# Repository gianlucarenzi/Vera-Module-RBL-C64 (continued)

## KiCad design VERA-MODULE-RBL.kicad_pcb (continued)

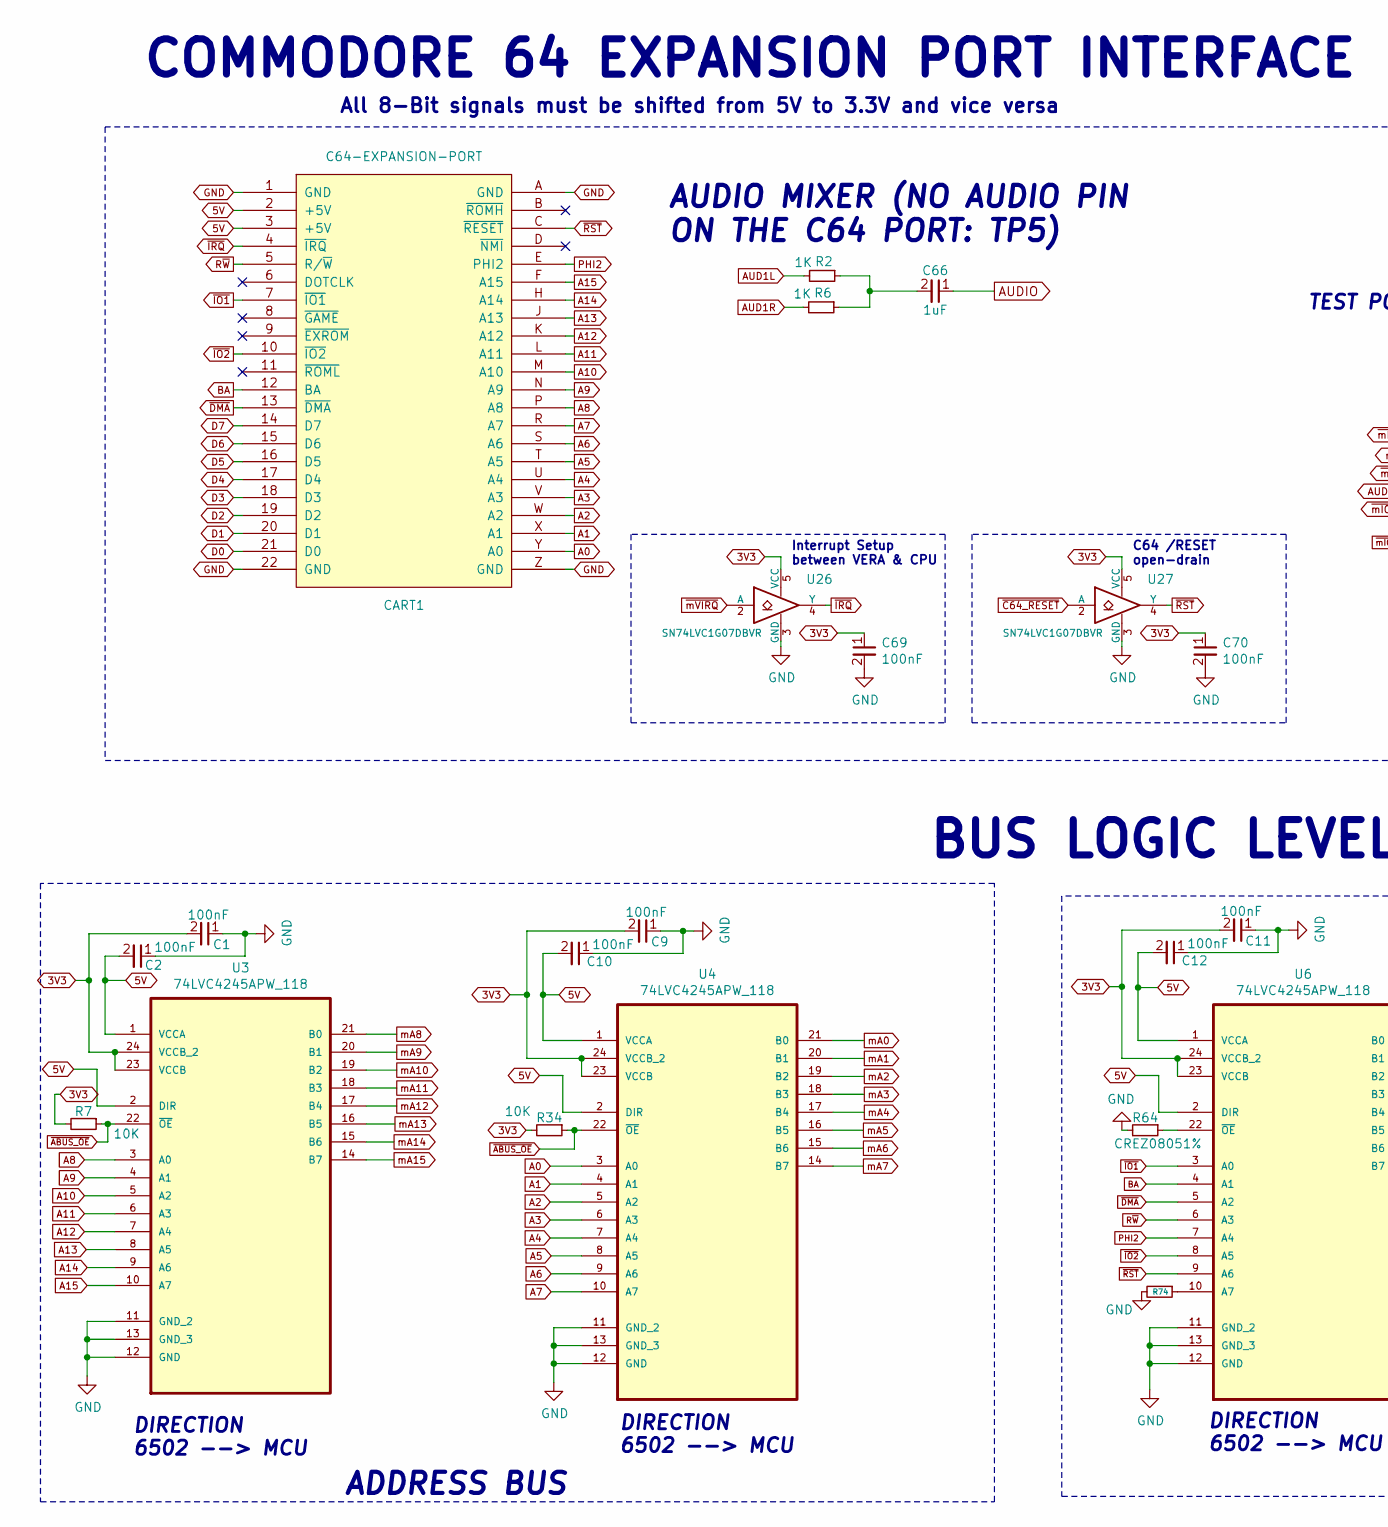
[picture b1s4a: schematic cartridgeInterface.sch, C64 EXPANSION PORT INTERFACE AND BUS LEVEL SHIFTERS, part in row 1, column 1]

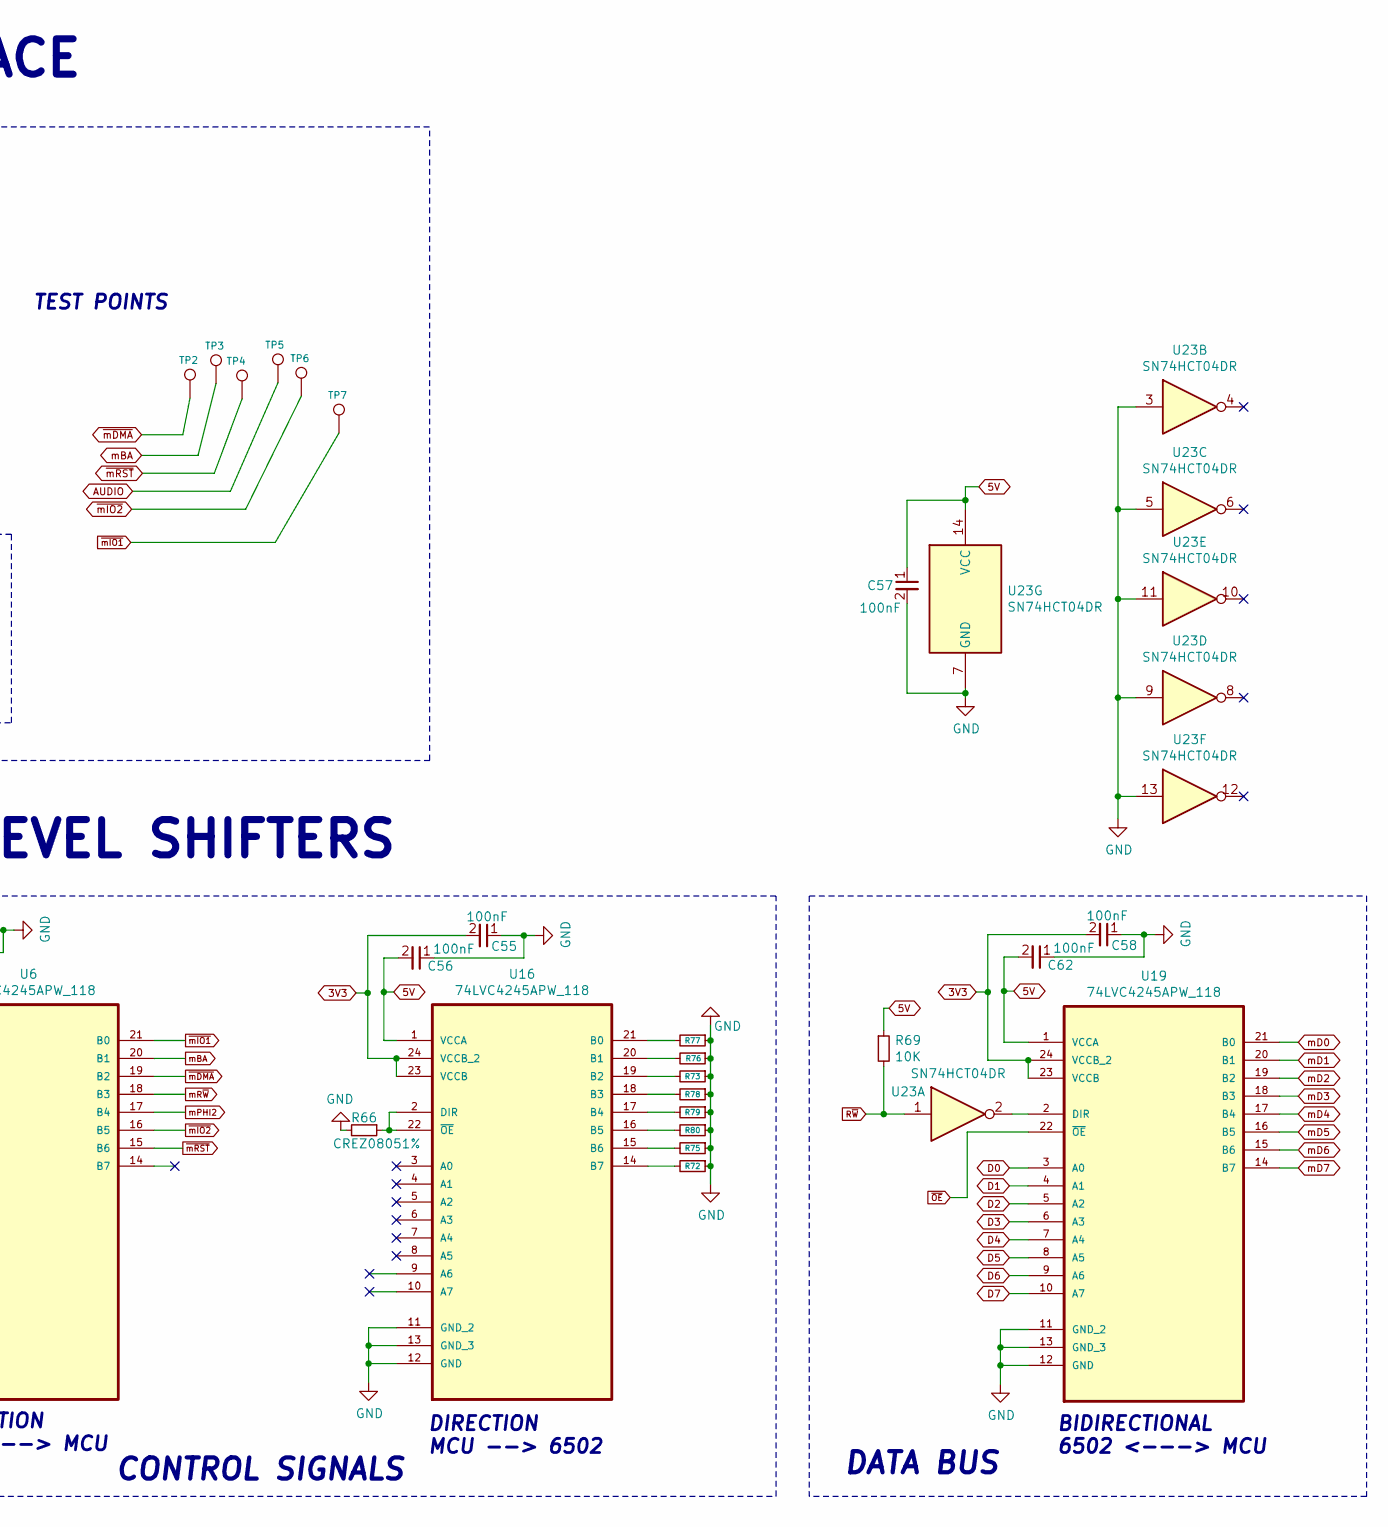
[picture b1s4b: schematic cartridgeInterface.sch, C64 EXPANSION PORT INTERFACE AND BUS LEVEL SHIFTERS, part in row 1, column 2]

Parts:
C1, C2, C9, C10, C11, C12, C55, C56, C57, C58, C62, C69, C70: 100nF; C_0805_2012Metric_Pad1.18x1.45mm_HandSolder; LCSC C840116
C66: 1uF; C_0805_2012Metric_Pad1.18x1.45mm_HandSolder; LCSC C2798196
CART1: C64-EXPANSION-PORT; C64-EXPANSION-CARTRIDGE
R2, R6: 1K; R_0805_2012Metric_Pad1.20x1.40mm_HandSolder; LCSC C17513
R7, R34, R69: 10K; R_0805_2012Metric_Pad1.20x1.40mm_HandSolder; LCSC C84376
R64, R66, R72, R73, R74, R75, R76, R77, R78, R79, R80: CREZ08051%; R_0805_2012Metric_Pad1.20x1.40mm_HandSolder; LCSC C328378
TP2, TP3, TP4, TP5, TP6, TP7: TestPoint; TestPoint_Pad_D2.0mm
U3, U4, U6, U16, U19: 74LVC4245APW_118; IC_74LVC4245_SOP65P640X110-24N; LCSC C6091
U23: SN74HCT04DR; SOIC-14_3.9x8.7mm_P1.27mm; LCSC C6766
U26, U27: SN74LVC1G07DBVR; SOT-23-5; LCSC C7829

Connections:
3V3: C1.2, C9.2, C11.2, C55.2, C58.2, C69.1, C70.1, R7.2, R34.2, U3.23 (VCCB), U3.24 (VCCB_2), U4.23 (VCCB), U4.24 (VCCB_2), U6.23 (VCCB), U6.24 (VCCB_2), U16.23 (VCCB), U16.24 (VCCB_2), U19.23 (VCCB), U19.24 (VCCB_2), U26.5 (VCC), U27.5 (VCC); also elsewhere on the board
5V: C2.2, C10.2, C12.2, C56.2, C57.1, C62.2, CART1.2 (+5V), CART1.3 (+5V), R69.1, U3.1 (VCCA), U3.2 (DIR), U4.1 (VCCA), U4.2 (DIR), U6.1 (VCCA), U6.2 (DIR), U16.1 (VCCA), U19.1 (VCCA), U23.14 (VCC); also elsewhere on the board
A0: CART1.Y (A0), U4.3 (A0)
A1: CART1.X (A1), U4.4 (A1)
A2: CART1.W (A2), U4.5 (A2)
A3: CART1.V (A3), U4.6 (A3)
A4: CART1.U (A4), U4.7 (A4)
A5: CART1.T (A5), U4.8 (A5)
A6: CART1.S (A6), U4.9 (A6)
A7: CART1.R (A7), U4.10 (A7)
A8: CART1.P (A8), U3.3 (A0)
A9: CART1.N (A9), U3.4 (A1)
A10: CART1.M (A10), U3.5 (A2)
A11: CART1.L (A11), U3.6 (A3)
A12: CART1.K (A12), U3.7 (A4)
A13: CART1.J (A13), U3.8 (A5)
A14: CART1.H (A14), U3.9 (A6)
A15: CART1.F (A15), U3.10 (A7)
AUD1L: R2.2; also elsewhere on the board
AUD1R: R6.2; also elsewhere on the board
AUDIO: C66.1, TP5.1
BA: CART1.12 (BA), U6.4 (A1)
D0: CART1.21 (D0), U19.3 (A0)
D1: CART1.20 (D1), U19.4 (A1)
D2: CART1.19 (D2), U19.5 (A2)
D3: CART1.18 (D3), U19.6 (A3)
D4: CART1.17 (D4), U19.7 (A4)
D5: CART1.16 (D5), U19.8 (A5)
D6: CART1.15 (D6), U19.9 (A6)
D7: CART1.14 (D7), U19.10 (A7)
GND: C1.1, C2.1, C9.1, C10.1, C11.1, C12.1, C55.1, C56.1, C57.2, C58.1, C62.1, C69.2, C70.2, CART1.1 (GND), CART1.22 (GND), CART1.A (GND), CART1.Z (GND), R64.2, R66.2, R72.1, R73.1, R74.2, R75.1, R76.1, R77.1, R78.1, R79.1, R80.1, U3.11 (GND_2), U3.12 (GND), U3.13 (GND_3), U4.11 (GND_2), U4.12 (GND), U4.13 (GND_3), U6.11 (GND_2), U6.12 (GND), U6.13 (GND_3), U16.11 (GND_2), U16.12 (GND), U16.13 (GND_3), U19.11 (GND_2), U19.12 (GND), U19.13 (GND_3), U23.3, U23.5, U23.7 (GND), U23.9, U23.11, U23.13, U26.3 (GND), U27.3 (GND); also elsewhere on the board
unnamed: C66.2, R2.1, R6.1
unnamed: R64.1, U6.22 (~OE)
unnamed: R66.1, U16.2 (DIR), U16.22 (~OE)
unnamed: R72.2, U16.14 (B7)
unnamed: R73.2, U16.19 (B2)
unnamed: R74.1, U6.10 (A7)
unnamed: R75.2, U16.15 (B6)
unnamed: R76.2, U16.20 (B1)
unnamed: R77.2, U16.21 (B0)
unnamed: R78.2, U16.18 (B3)
unnamed: R79.2, U16.17 (B4)
unnamed: R80.2, U16.16 (B5)
unnamed: U19.2 (DIR), U23.2
PHI2: CART1.E (PHI2), U6.7 (A4)
R~W: CART1.5 (R/~W), R69.2, U6.6 (A3), U23.1
mA0: U4.21 (B0); also elsewhere on the board
mA1: U4.20 (B1); also elsewhere on the board
mA2: U4.19 (B2); also elsewhere on the board
mA3: U4.18 (B3); also elsewhere on the board
mA4: U4.17 (B4); also elsewhere on the board
mA5: U4.16 (B5); also elsewhere on the board
mA6: U4.15 (B6); also elsewhere on the board
mA7: U4.14 (B7); also elsewhere on the board
mA8: U3.21 (B0); also elsewhere on the board
mA9: U3.20 (B1); also elsewhere on the board
mA10: U3.19 (B2); also elsewhere on the board
mA11: U3.18 (B3); also elsewhere on the board
mA12: U3.17 (B4); also elsewhere on the board
mA13: U3.16 (B5); also elsewhere on the board
mA14: U3.15 (B6); also elsewhere on the board
mA15: U3.14 (B7); also elsewhere on the board
mBA: TP3.1, U6.20 (B1)
mD0: U19.21 (B0); also elsewhere on the board
mD1: U19.20 (B1); also elsewhere on the board
mD2: U19.19 (B2); also elsewhere on the board
mD3: U19.18 (B3); also elsewhere on the board
mD4: U19.17 (B4); also elsewhere on the board
mD5: U19.16 (B5); also elsewhere on the board
mD6: U19.15 (B6); also elsewhere on the board
mD7: U19.14 (B7); also elsewhere on the board
mPHI2: U6.17 (B4); also elsewhere on the board
mR~W: U6.18 (B3); also elsewhere on the board
~ABUS_OE: R7.1, R34.1, U3.22 (~OE), U4.22 (~OE); also elsewhere on the board
~C64_RESET: U27.2 (A); also elsewhere on the board
~DMA: CART1.13 (~DMA), U6.5 (A2)
~IO1: CART1.7 (~IO1), U6.3 (A0)
~IO2: CART1.10 (~IO2), U6.8 (A5)
~IRQ: CART1.4 (~IRQ), U26.4 (Y)
~OE: U19.22 (~OE); also elsewhere on the board
~RST: CART1.C (~RESET), U6.9 (A6), U27.4 (Y)
~mDMA: TP2.1, U6.19 (B2)
~mIO1: TP7.1, U6.21 (B0); also elsewhere on the board
~mIO2: TP6.1, U6.16 (B5); also elsewhere on the board
~mRST: TP4.1, U6.15 (B6)
~mVIRQ: U26.2 (A); also elsewhere on the board

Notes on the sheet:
COMMODORE 64 EXPANSION PORT INTERFACE
All 8-Bit signals must be shifted from 5V to 3.3V and vice versa
TEST POINTS
BUS LOGIC LEVEL SHIFTERS
DIRECTION 6502 --> MCU
DIRECTION MCU --> 6502
BIDIRECTIONAL 6502 <---> MCU
CONTROL SIGNALS
ADDRESS BUS
DATA BUS
Interrupt Setup between VERA & CPU
C64 /RESET open-drain
AUDIO MIXER (NO AUDIO PIN ON THE C64 PORT: TP5)

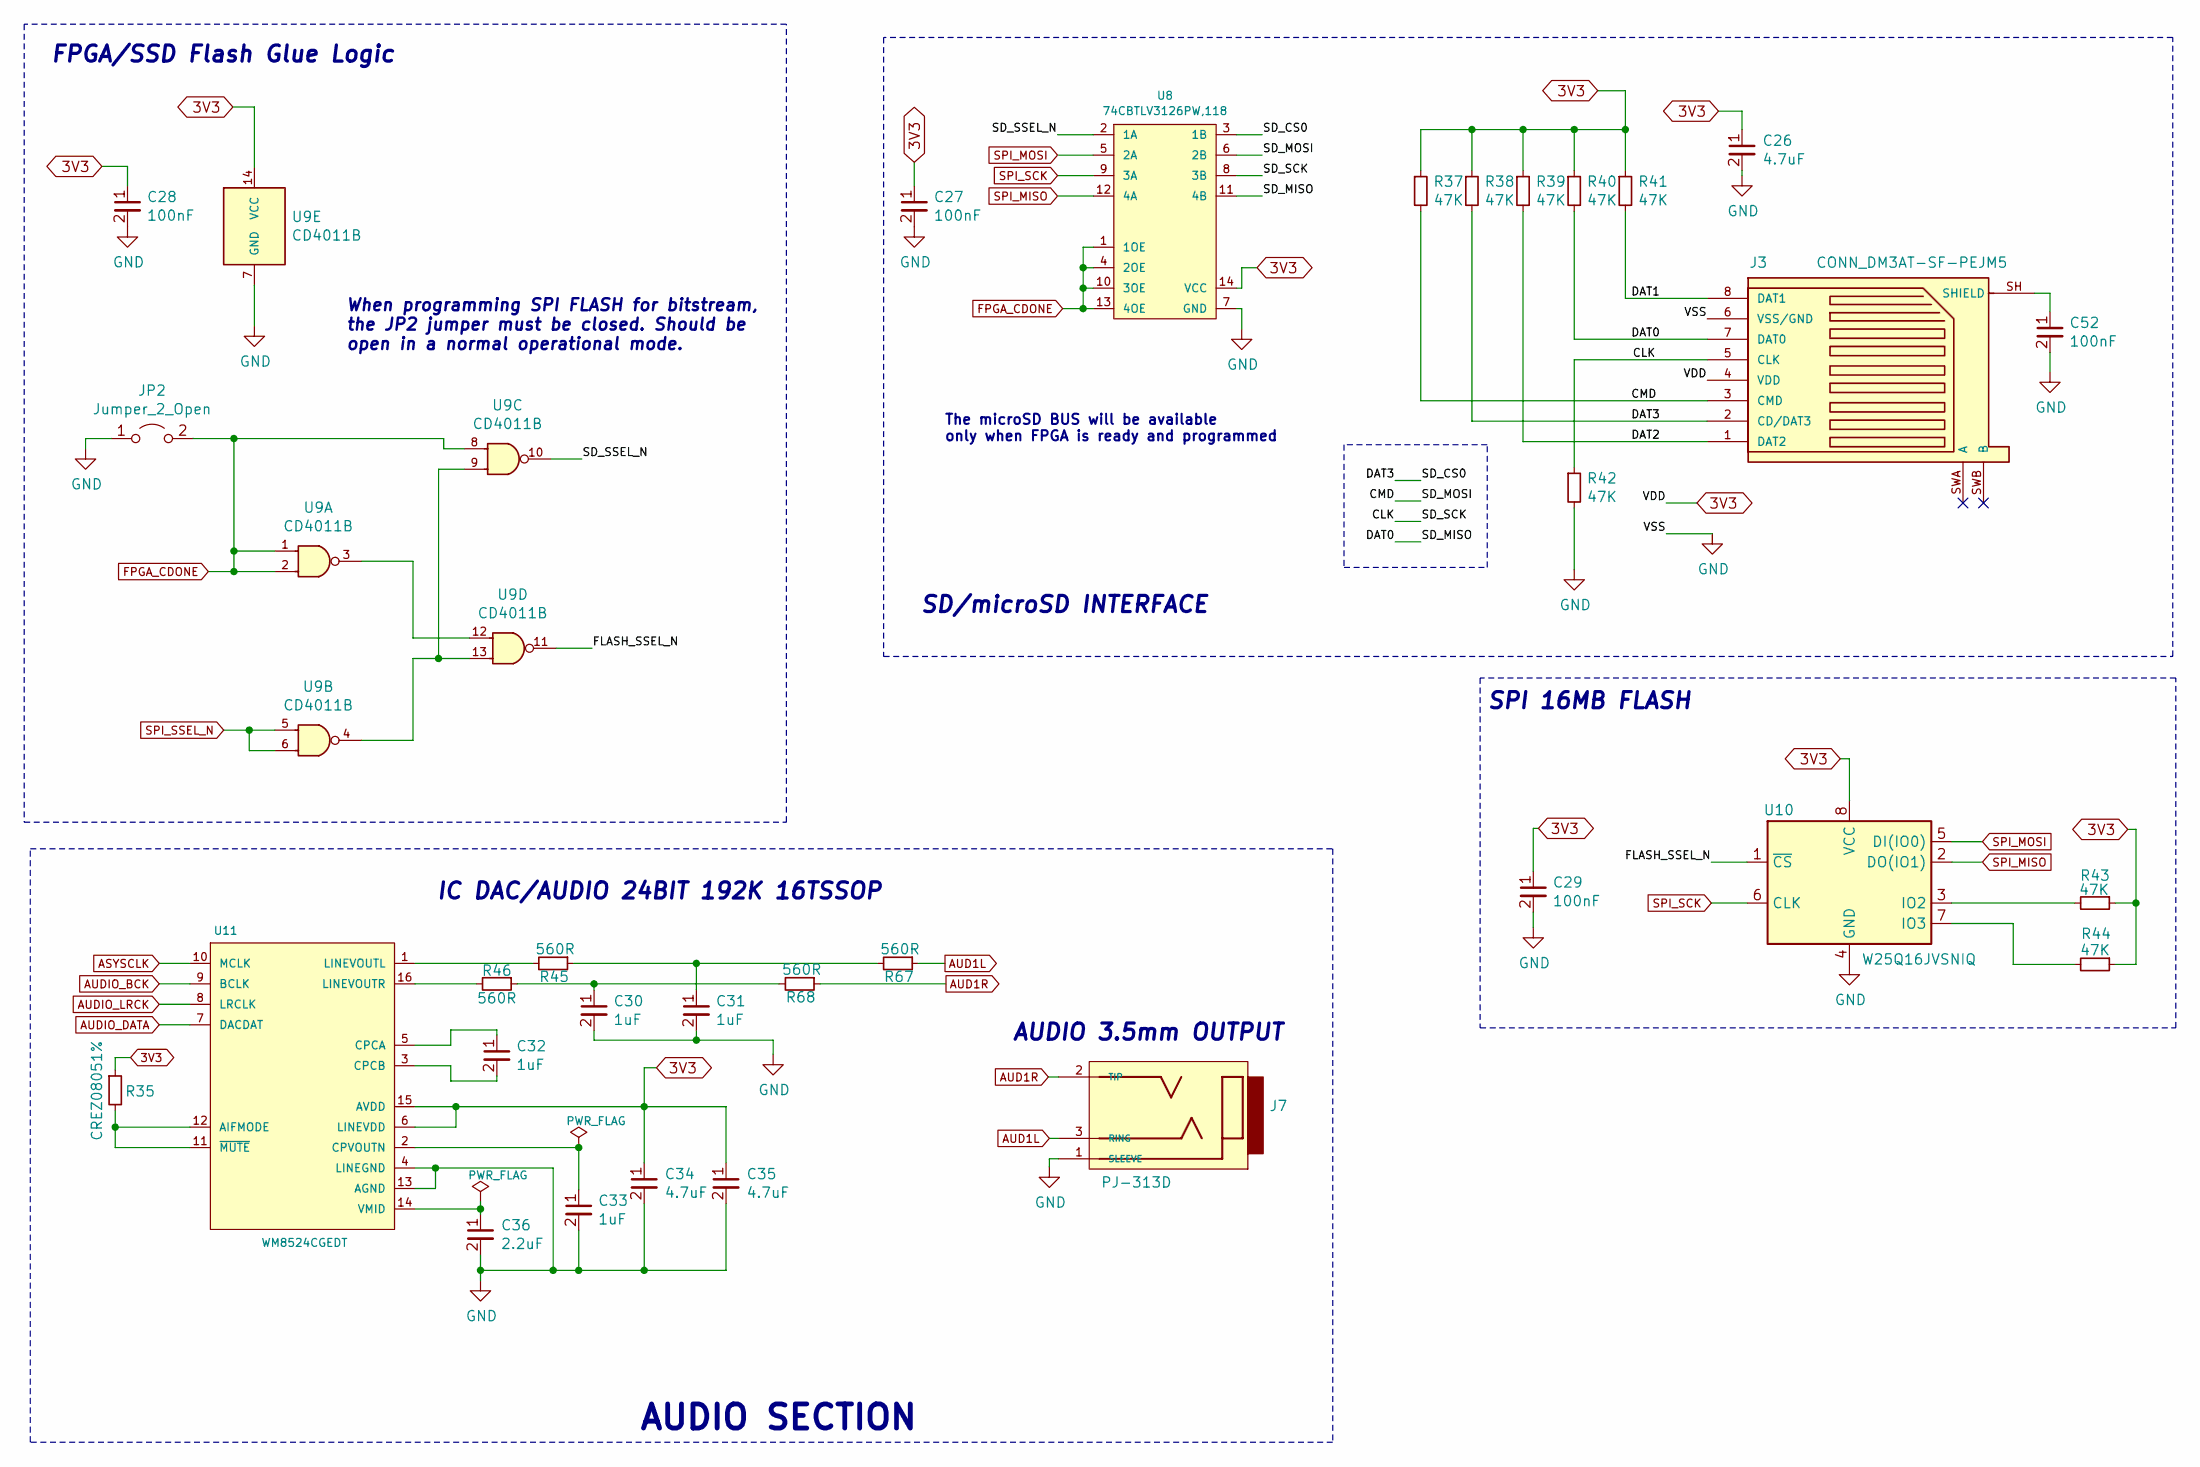
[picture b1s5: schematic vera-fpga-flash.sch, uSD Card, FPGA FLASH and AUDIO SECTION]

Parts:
C26, C34, C35: 4.7uF; C_0805_2012Metric_Pad1.18x1.45mm_HandSolder; LCSC C7393930
C27, C28, C29, C52: 100nF; C_0805_2012Metric_Pad1.18x1.45mm_HandSolder; LCSC C840116
C30, C31, C32, C33: 1uF; C_0805_2012Metric_Pad1.18x1.45mm_HandSolder; LCSC C2798196
C36: 2.2uF; C_0805_2012Metric_Pad1.18x1.45mm_HandSolder; LCSC C377773
J3: CONN_DM3AT-SF-PEJM5; HRS_DM3AT-SF-PEJM5; PARTREV 20200913; LCSC C114218
J7: PJ-313D; jack_3.5_pj313d-smt; LCSC C668608
JP2: Jumper_2_Open; PinHeader_1x02_P2.54mm_Vertical
R35: CREZ08051%; R_0805_2012Metric_Pad1.20x1.40mm_HandSolder; LCSC C328378
R37, R38, R39, R40, R41, R42, R43, R44: 47K; R_0805_2012Metric_Pad1.20x1.40mm_HandSolder; LCSC C17713
R45, R46, R67, R68: 560R; R_0805_2012Metric_Pad1.20x1.40mm_HandSolder; LCSC C28636
U8: 74CBTLV3126PW,118; TSSOP-14_4.4x5mm_P0.65mm; LCSC C543078
U9: CD4011B; SOIC-14_3.9x8.7mm_P1.27mm; LCSC C194334
U10: W25Q16JVSNIQ; SOIC-8_3.9x4.9mm_P1.27mm; LCSC C2456211
U11: WM8524CGEDT; TSSOP-16_4.4x5mm_P0.65mm; LCSC C146242

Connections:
3V3: C26.1, C27.1, C28.1, C29.1, C34.1, C35.1, J3.4 (VDD), R35.1, R37.1, R38.1, R39.1, R40.1, R41.1, R43.1, R44.1, U8.14 (VCC), U9.14 (VCC), U10.8 (VCC), U11.6 (LINEVDD), U11.15 (AVDD); also elsewhere on the board
/Vera FPGA flash/CLK: J3.5 (CLK), R42.1, U8.8 (3B)
/Vera FPGA flash/CMD: J3.3 (CMD), R37.2, U8.6 (2B)
/Vera FPGA flash/DAT0: J3.7 (DAT0), R40.2, U8.11 (4B)
/Vera FPGA flash/DAT1: J3.8 (DAT1), R41.2
/Vera FPGA flash/DAT2: J3.1 (DAT2), R39.2
/Vera FPGA flash/DAT3: J3.2 (CD/DAT3), R38.2, U8.3 (1B)
/Vera FPGA flash/FLASH_SSEL_N: U9.11 (4Y), U10.1 (~CS)
/Vera FPGA flash/SD_SSEL_N: U8.2 (1A), U9.10 (4Y)
ASYSCLK: U11.10 (MCLK); also elsewhere on the board
AUD1L: J7.3 (RING), R67.1; also elsewhere on the board
AUD1R: J7.2 (TIP), R68.1; also elsewhere on the board
AUDIO_BCK: U11.9 (BCLK); also elsewhere on the board
AUDIO_DATA: U11.7 (DACDAT); also elsewhere on the board
AUDIO_LRCK: U11.8 (LRCLK); also elsewhere on the board
FPGA_CDONE: JP2.2 (B), U8.1 (1OE), U8.4 (2OE), U8.10 (3OE), U8.13 (4OE), U9.1 (4A), U9.2 (4B), U9.8 (4A); also elsewhere on the board
GND: C26.2, C27.2, C28.2, C29.2, C30.2, C31.2, C33.2, C34.2, C35.2, C36.2, C52.2, J3.6 (VSS/GND), J7.1 (SLEEVE), JP2.1 (A), R42.2, U8.7 (GND), U9.7 (GND), U10.4 (GND), U11.4 (LINEGND), U11.13 (AGND); also elsewhere on the board
unnamed: C30.1, R46.1, R68.2
unnamed: C31.1, R45.1, R67.2
unnamed: C32.1, U11.5 (CPCA)
unnamed: C32.2, U11.3 (CPCB)
unnamed: C33.1, U11.2 (CPVOUTN)
unnamed: C36.1, U11.14 (VMID)
unnamed: C52.1, J3.SH (SHIELD)
unnamed: R35.2, U11.11 (~MUTE), U11.12 (AIFMODE)
unnamed: R43.2, U10.3 (IO2)
unnamed: R44.2, U10.7 (IO3)
unnamed: R45.2, U11.1 (LINEVOUTL)
unnamed: R46.2, U11.16 (LINEVOUTR)
unnamed: U9.3 (4Y), U9.12 (4A)
unnamed: U9.4 (4Y), U9.9 (4B), U9.13 (4B)
SPI_MISO: U8.12 (4A), U10.2 (DO(IO1)); also elsewhere on the board
SPI_MOSI: U8.5 (2A), U10.5 (DI(IO0)); also elsewhere on the board
SPI_SCK: U8.9 (3A), U10.6 (CLK); also elsewhere on the board
SPI_SSEL_N: U9.5 (4A), U9.6 (4B); also elsewhere on the board

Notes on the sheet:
IC DAC/AUDIO 24BIT 192K 16TSSOP
SD/microSD INTERFACE
FPGA/SSD Flash Glue Logic
SPI 16MB FLASH
The microSD BUS will be available only when FPGA is ready and programmed
When programming SPI FLASH for bitstream, the JP2 jumper must be closed. Should be open in a normal operational mode.
AUDIO 3.5mm OUTPUT
AUDIO SECTION

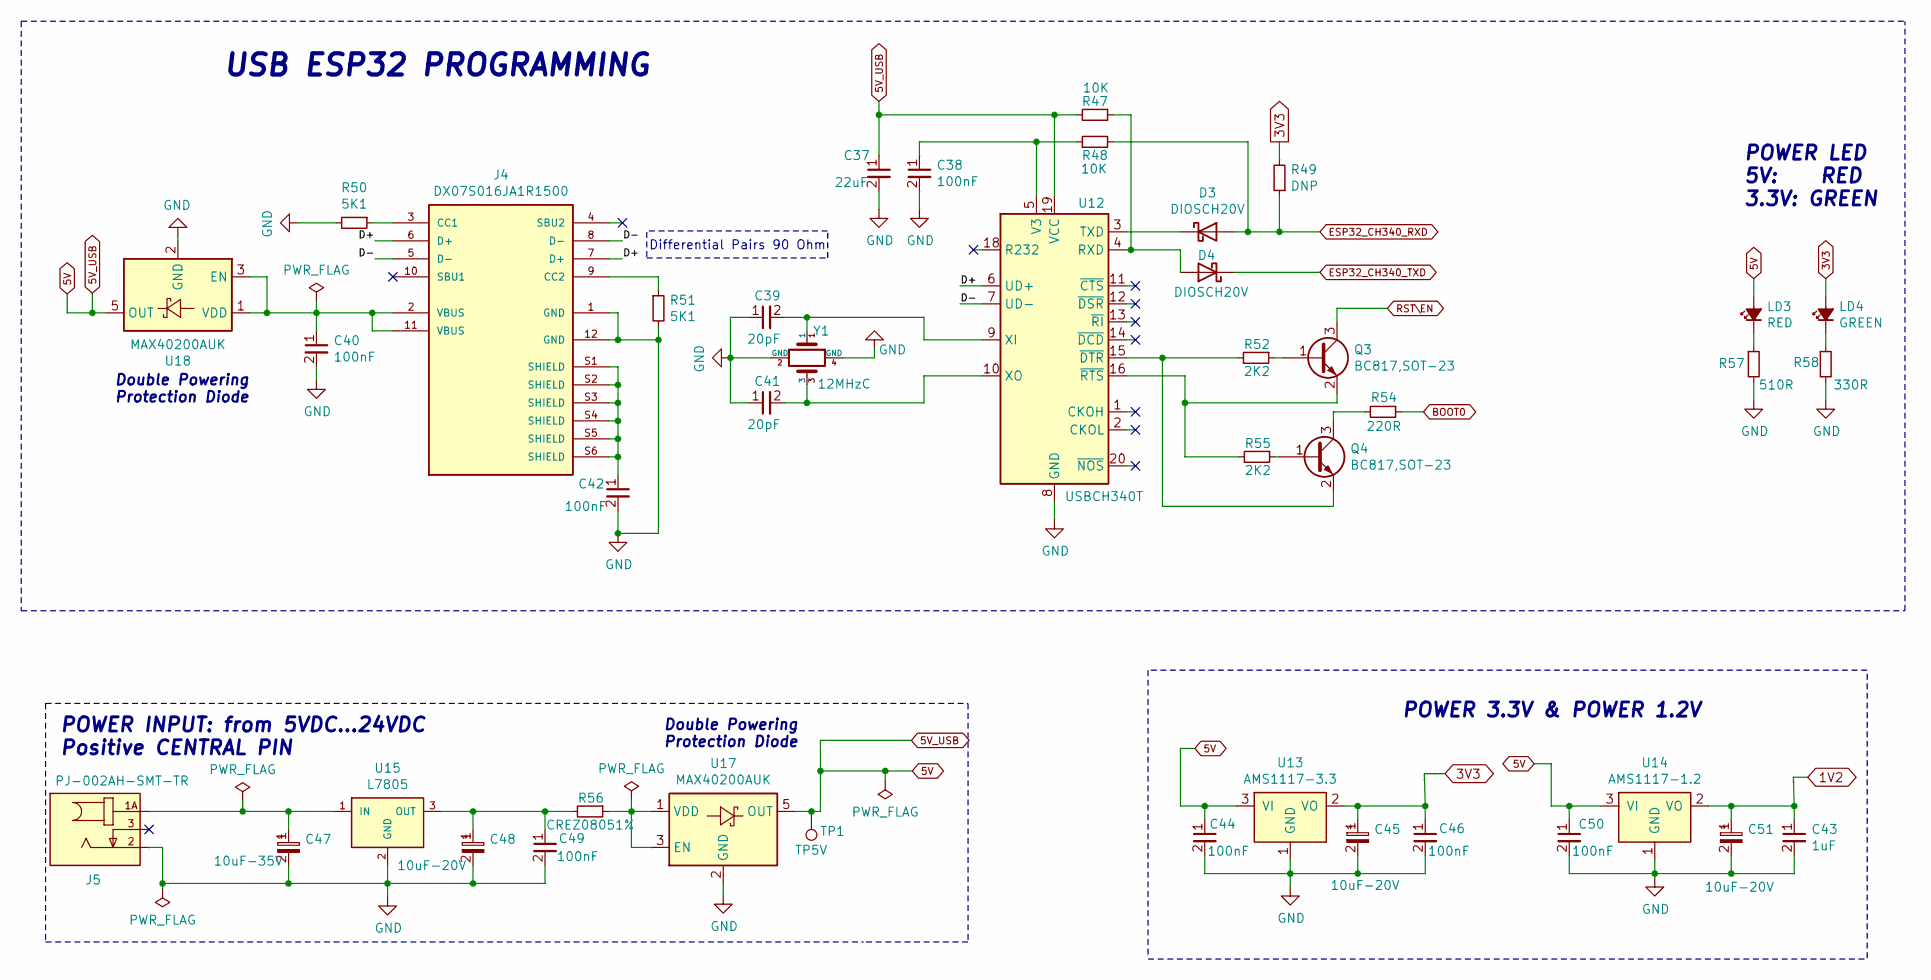
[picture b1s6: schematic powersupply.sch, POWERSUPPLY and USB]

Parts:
C37: 22uF; C_0805_2012Metric_Pad1.18x1.45mm_HandSolder; LCSC C86817
C38, C40, C42, C44, C46, C49, C50: 100nF; C_0805_2012Metric_Pad1.18x1.45mm_HandSolder; LCSC C840116
C39, C41: 20pF; C_0805_2012Metric_Pad1.18x1.45mm_HandSolder; LCSC C376875
C43: 1uF; C_0805_2012Metric_Pad1.18x1.45mm_HandSolder; LCSC C2798196
C45, C48, C51: 10uF-20V; CP_EIA-3528-12_Kemet-T_Pad1.50x2.35mm_HandSolder; LCSC C8017
C47: 10uF-35V; CP_EIA-3528-12_Kemet-T_Pad1.50x2.35mm_HandSolder; LCSC C8017
D3, D4: DIOSCH20V; D_SMC_Handsoldering; LCSC C236151
J4: DX07S016JA1R1500; JAE_DX07S016JA1R1500; PARTREV 1; LCSC C3197885
J5: PJ-002AH-SMT-TR; CUI_PJ-002AH-SMT-TR; LCSC C22434687
LD3: RED; LED_1206_3216Metric_Pad1.42x1.75mm_HandSolder; LCSC C965822
LD4: GREEN; LED_0805_2012Metric_Pad1.15x1.40mm_HandSolder; LCSC C84260
Q3, Q4: BC817,SOT-23; SOT-23; LCSC C20069154
R47, R48: 10K; R_0805_2012Metric_Pad1.20x1.40mm_HandSolder; LCSC C84376
R49: DNP; R_1206_3216Metric_Pad1.30x1.75mm_HandSolder
R50, R51: 5K1; R_0805_2012Metric_Pad1.20x1.40mm_HandSolder; LCSC C27834
R52, R55: 2K2; R_0805_2012Metric_Pad1.20x1.40mm_HandSolder; LCSC C17520
R54: 220R; R_0805_2012Metric_Pad1.20x1.40mm_HandSolder; LCSC C5120092
R56: CREZ08051%; R_0805_2012Metric_Pad1.20x1.40mm_HandSolder; LCSC C328378
R57: 510R; R_0805_2012Metric_Pad1.20x1.40mm_HandSolder; LCSC C114563
R58: 330R; R_0603_1608Metric_Pad0.98x0.95mm_HandSolder; LCSC C105881
TP1: TP5V; TestPoint_Pad_D2.0mm
U12: USBCH340T; SSOP-20_5.3x7.2mm_P0.65mm_Pad0.45; LCSC C8689
U13: AMS1117-3.3; SOT-223-3_TabPin2; LCSC C6186
U14: AMS1117-1.2; SOT-223-3_TabPin2; LCSC C347218
U15: L7805; TO-252-2; LCSC C110908
U17, U18: MAX40200AUK; SOT-23-5; LCSC C47118006
Y1: 12MHzC; Crystal_SMD_EuroQuartz_MT-4Pin_3.2x2.5mm; LCSC C9002

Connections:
1V2: C43.1, C51.1, U14.2 (VO); also elsewhere on the board
3V3: C45.1, C46.1, LD4.2 (A), R49.2, U13.2 (VO); also elsewhere on the board
5V: C37.1, C44.1, C50.1, LD3.2 (A), R47.2, TP1.1, U12.19 (VCC), U13.3 (VI), U14.3 (VI), U17.5 (OUT), U18.5 (OUT); also elsewhere on the board
/PowerSupply/D+: J4.6 (D+), J4.7 (D+), U12.6 (UD+)
/PowerSupply/D-: J4.5 (D-), J4.8 (D-), U12.7 (UD-)
BOOT0: R54.1; also elsewhere on the board
ESP32_CH340_RXD: D3.2 (A), R48.2, R49.1; also elsewhere on the board
ESP32_CH340_TXD: D4.1 (K); also elsewhere on the board
GND: C37.2, C38.2, C39.1, C40.2, C41.1, C42.2, C43.2, C44.2, C45.2, C46.2, C47.2, C48.2, C49.2, C50.2, C51.2, J4.1 (GND), J4.12 (GND), J5.2, R50.2, R51.2, R57.2, R58.2, U12.8 (GND), U13.1 (GND), U14.1 (GND), U15.2 (GND), U17.2 (GND), U18.2 (GND), Y1.2 (GND), Y1.4 (GND); also elsewhere on the board
unnamed: C38.1, R48.1, U12.5 (V3)
unnamed: C39.2, U12.9 (XI), Y1.1
unnamed: C40.1, J4.2 (VBUS), J4.11 (VBUS), U18.1 (VDD), U18.3 (EN)
unnamed: C41.2, U12.10 (XO), Y1.3
unnamed: C42.1, J4.S1 (SHIELD), J4.S2 (SHIELD), J4.S3 (SHIELD), J4.S4 (SHIELD), J4.S5 (SHIELD), J4.S6 (SHIELD)
unnamed: C47.1, J5.1A, J5.1B, U15.1 (IN)
unnamed: C48.1, C49.1, R56.2, U15.3 (OUT)
unnamed: D3.1 (K), U12.3 (TXD)
unnamed: D4.2 (A), R47.1, U12.4 (RXD)
unnamed: J4.3 (CC1), R50.1
unnamed: J4.9 (CC2), R51.1
unnamed: LD3.1 (K), R57.1
unnamed: LD4.1 (K), R58.1
unnamed: Q3.1 (B), R52.1
unnamed: Q3.2 (E), R55.2, U12.16 (~RTS)
unnamed: Q4.1 (B), R55.1
unnamed: Q4.2 (E), R52.2, U12.15 (~DTR)
unnamed: Q4.3 (C), R54.2
unnamed: R56.1, U17.1 (VDD), U17.3 (EN)
RST\EN: Q3.3 (C); also elsewhere on the board

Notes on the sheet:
POWER INPUT: from 5VDC...24VDC Positive CENTRAL PIN
USB ESP32 PROGRAMMING
POWER 3.3V & POWER 1.2V
POWER LED 5V: RED 3.3V: GREEN
Differential Pairs 90 Ohm
Double Powering Protection Diode

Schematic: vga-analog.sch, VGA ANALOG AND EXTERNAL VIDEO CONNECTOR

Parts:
C53, C54: 100nF; C_0805_2012Metric_Pad1.18x1.45mm_HandSolder; LCSC C840116
J1: CONN_SMD_HEADER_BOX_02x08_HX-JN2.54; IDC-Header_2x08_P2.54mm_Vertical_SMD; LCSC C41376031
J2: DS1038-15FBNSiA74-0CC; CONNFLY_DS1038-15FBNSIA74-0CC; LCSC C75754
R8, R9, R10: 4K3; R_0805_2012Metric_Pad1.20x1.40mm_HandSolder; LCSC C17667
R11, R13, R15: 2K; R_0805_2012Metric_Pad1.20x1.40mm_HandSolder; LCSC C114572
R12, R14, R16: 150R; R_0805_2012Metric_Pad1.20x1.40mm_HandSolder; LCSC C17471
R17, R19, R21: 910R; R_0805_2012Metric_Pad1.20x1.40mm_HandSolder; LCSC C2930211
R18, R20, R22: 160R; R_0805_2012Metric_Pad1.20x1.40mm_HandSolder; LCSC C2960793
R23, R25, R27: 510R; R_0805_2012Metric_Pad1.20x1.40mm_HandSolder; LCSC C114563
R24, R26, R28: 27R; R_0805_2012Metric_Pad1.20x1.40mm_HandSolder; LCSC C17594
R29, R30: 820R; R_0805_2012Metric_Pad1.20x1.40mm_HandSolder; LCSC C17837

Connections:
3V3: J1.4, J1.16; also elsewhere on the board
5V: J1.9, J1.15, J2.9; also elsewhere on the board
AUD1L: J1.11; also elsewhere on the board
AUD1R: J1.12; also elsewhere on the board
GND: C53.1, C54.1, J1.5, J1.6, J1.7, J1.8, J1.10, J2.5, J2.6, J2.7, J2.8, J2.10; also elsewhere on the board
unnamed: C53.2, J2.S2 (SHIELD__1)
unnamed: C54.2, J2.S1 (SHIELD)
unnamed: R11.1, R12.2
unnamed: R13.1, R14.2
unnamed: R15.1, R16.2
unnamed: R17.1, R18.2
unnamed: R19.1, R20.2
unnamed: R21.1, R22.2
unnamed: R23.1, R24.2
unnamed: R25.1, R26.2
unnamed: R27.1, R28.2
VGABLUE: J1.3, J2.3, R8.1, R12.1, R18.1, R24.1
VGAGREEN: J1.2, J2.2, R9.1, R14.1, R20.1, R26.1
VGAHSYNC: J1.13, J2.13, R29.1
VGARED: J1.1, J2.1, R10.1, R16.1, R22.1, R28.1
VGAVSYNC: J1.14, J2.14, R30.1
VGA_B0: R8.2; also elsewhere on the board
VGA_B1: R11.2; also elsewhere on the board
VGA_B2: R17.2; also elsewhere on the board
VGA_B3: R23.2; also elsewhere on the board
VGA_G0: R9.2; also elsewhere on the board
VGA_G1: R13.2; also elsewhere on the board
VGA_G2: R19.2; also elsewhere on the board
VGA_G3: R25.2; also elsewhere on the board
VGA_HSYNC: R29.2; also elsewhere on the board
VGA_R0: R10.2; also elsewhere on the board
VGA_R1: R15.2; also elsewhere on the board
VGA_R2: R21.2; also elsewhere on the board
VGA_R3: R27.2; also elsewhere on the board
VGA_VSYNC: R30.2; also elsewhere on the board

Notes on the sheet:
EXTERNAL DISPLAY WITH AUDIO
ANALOG VGA SIGNALS
EXTERNAL VIDEO CONNECTOR

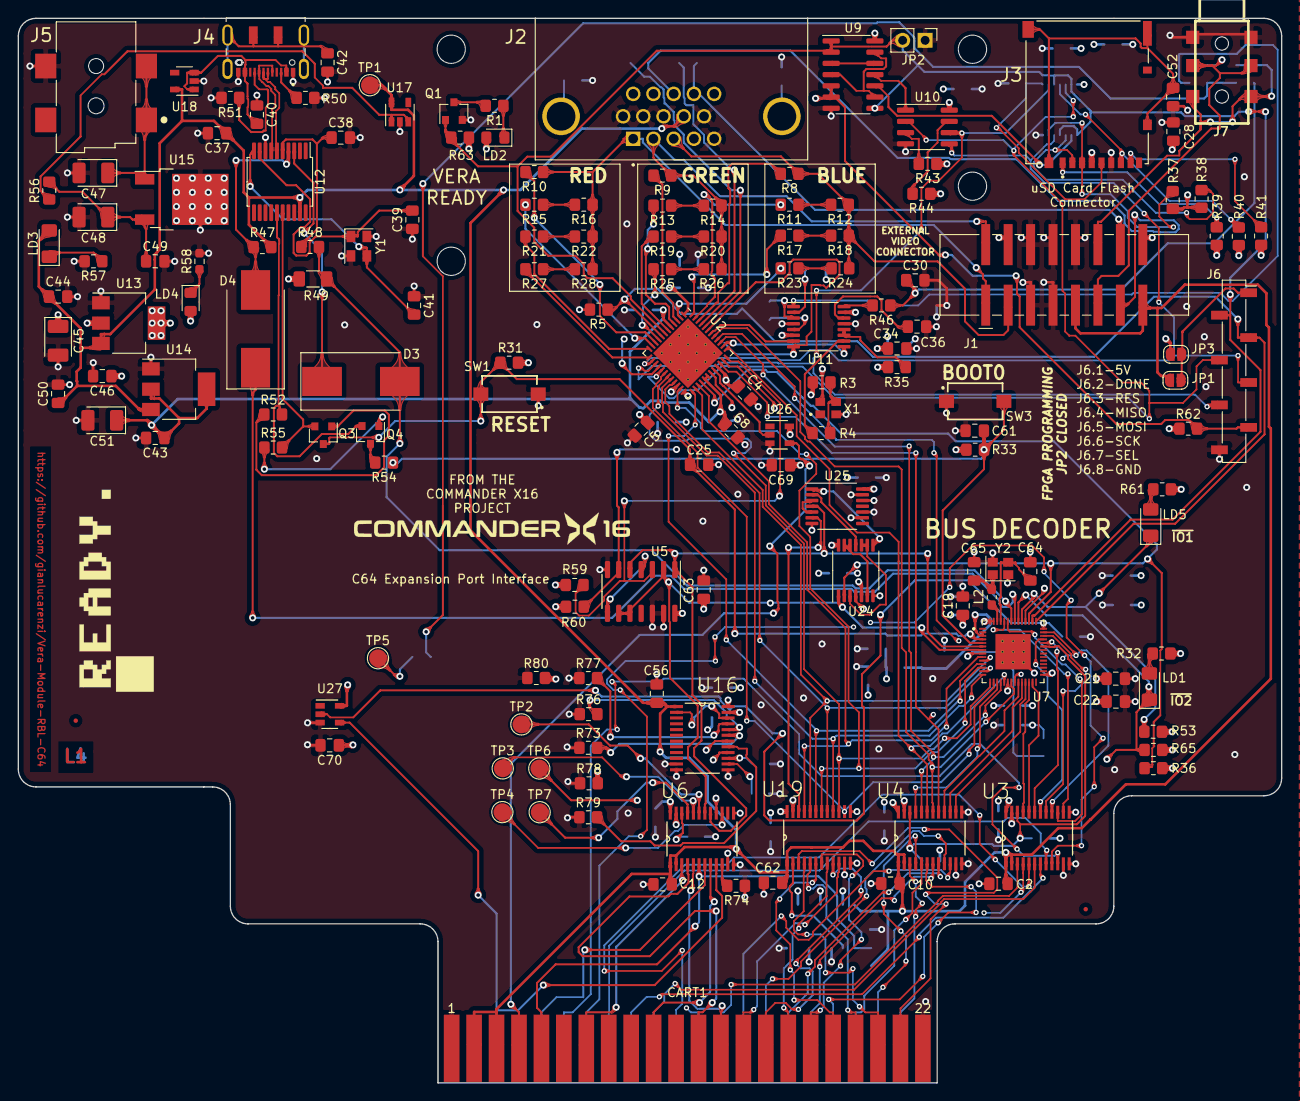
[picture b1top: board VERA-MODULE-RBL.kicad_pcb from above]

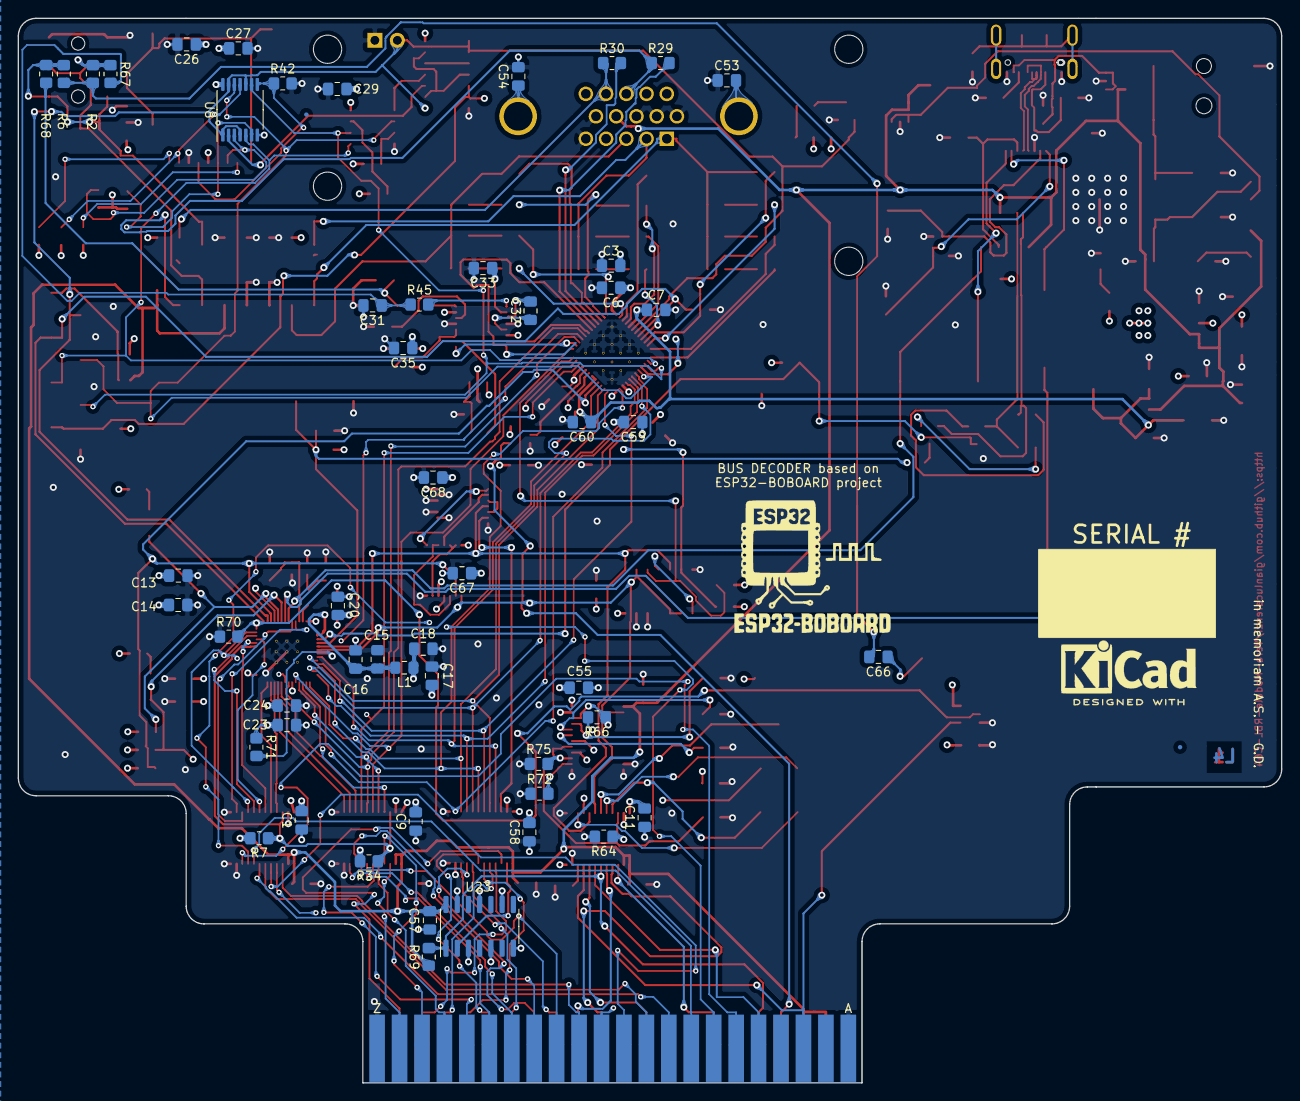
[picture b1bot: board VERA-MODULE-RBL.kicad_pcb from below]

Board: 4 copper layers, 143.0 x 120.5 mm, 221 parts (57 on the bottom side), 195 nets.

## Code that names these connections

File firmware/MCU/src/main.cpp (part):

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 * =========================================================================== */

/* --- Bank 0 Signals (GPIO 0-31) --- */
#define PIN_PHI2        1    /* CPU Clock Phase 2 (Pin 6) */
#define PIN_RW          2    /* Read/Write, High = Read (Pin 7) */

/* D0-D7: GPIO 4 to 11 (Pins 9-16, contiguous in Bank 0): D0 = GPIO 4 */
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#define PIN_A11         34   /* Address Bit 11 (Pin 39) */
#define PIN_A12         35   /* Address Bit 12 (Pin 40) */
#define PIN_A13         36   /* Address Bit 13 (Pin 41) */
#define PIN_ARESET      37   /* C64 /RESET via U27 open-drain, net ~C64_RESET, pull-down R70 (Pin 42) */
#define PIN_CRESET      38   /* Vera Chip Reset Output (Pin 43) */
#define PIN_CDONE       39   /* Vera Programmed Status Input (Pin 44) */
#define PIN_DEV_SEL_N   40   /* Vera Chip Select Output (Pin 45, active LOW) */
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 * code executes.  The levels must be valid when CHIP_PU rises and for
 * t_H = 3 ms after it (datasheet v2.2, §3, Table 3-2).
 *
 * GPIO0  —  Pin  5  |  Boot mode selection  |  Internal weak PULL-UP 45 kΩ
 *   Net BOOT0: R33 4.7 kΩ pull-up, BOOT button SW3, C61 100 nF, and R54 -> Q4
 *   (auto-reset from the programmer).  Not wired to any C64 signal.
 *   CHIP_PU has R31 4.7 kΩ + C25 1 µF (4.7 ms) against 0.47 ms on GPIO0, so
 *   GPIO0 is already HIGH when the reset is released.
 *   Sampled value: HIGH → SPI boot from embedded flash.  LOW (SW3 or Q4)
 *   → joint download boot, which also needs GPIO46 LOW (see below).
 *
 * GPIO3  —  Pin  8  |  JTAG signal source   |  NO internal pull
 *   Not used by the firmware.  R71 10 kΩ pull-up to 3V3 fixes it HIGH, as the
 *   datasheet requires (§3.4: no internal pull, must not be left floating).
 *   Table 3-5: with the default eFuses GPIO3 is ignored and JTAG goes to the
 *   USB Serial/JTAG Controller; HIGH keeps that choice even if
 *   EFUSE_STRAP_JTAG_SEL is burned, so GPIO39-42 never become JTAG pins.
 *
 * GPIO45 —  Pin 51  |  VDD_SPI voltage      |  Internal weak PULL-DOWN 45 kΩ
 * GPIO46 —  Pin 52  |  ROM messages / download mode | Internal weak PULL-DOWN 45 kΩ
 *   A14 and A15, from the expansion port through U3 (74LVC4245).  The port
 *   address lines are always driven: by the 6510 (which keeps driving them
 *   while in reset) or, during PHI1 and VIC-II DMA, by the VIC-II and the
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 *   PIN_ABUS_OE_N (GPIO47) drives ~OE of U3 and U4, and R7/R34 (10 kΩ to 3V3)
 *   hold it HIGH while the ESP32 is in reset (GPIO47 has no pull and no
 *   power-up glitch).  With U3 disabled its outputs are high-Z and the
 *   internal pull-downs read GPIO45 = GPIO46 = LOW at every chip reset:
 *     GPIO45 LOW → VDD_SPI = 3.3 V from VDD3P3_RTC (Table 3-4), the voltage
 *                  of the FN8 in-package flash (HIGH = 1.8 V: no boot);
 *     GPIO46 LOW → ROM messages suppressed; together with GPIO0 LOW it gives
 *                  the joint download boot (GPIO0 LOW + GPIO46 HIGH is
 *                  invalid), so flashing works with the C64 running.
 *   setup() drives PIN_ABUS_OE_N LOW long after the 3 ms hold time; until
 *   then A0-A15 read as LOW or floating: the bus loop starts only afterwards.
 *   Disabling U4 as well also avoids driving GPIO12-19 against U4 during
 *   their power-up glitches (Table 2-2).
 */

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 * (ee.get_gpio_in / ee.wr_mask_gpio_out bypass the APB bus: ~1 cycle).
 *
 * Input channels  (bit index in cpu_ll_read_dedic_gpio_in() result):
 *   Ch 0 = PHI2 (GPIO 1), Ch 1 = R/W (GPIO 2), Ch 2 = /IO1 (GPIO 41),
 *   Ch 3 = /IO2 (GPIO 42)
 *   The GPIO matrix feeds the dedicated inputs without taking the pins away:
 *   the same signals stay visible in GPIO.in / GPIO.in1.
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}

/*
 * PHI2 edge waits: one ee.get_gpio_in and one bit branch per sample
 * (3 cycles), the shortest polling loop.
 */
static inline __attribute__((always_inline)) void wait_phi2_high(void)
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     * Input  bundle: [PHI2, R/W, /IO1, /IO2]  → input  ch 0-3
     * Output bundle: [DEV_SEL_N]              → output ch 0
     */
    static const int dedic_in_pins[]  = { PIN_PHI2, PIN_RW, PIN_IO1_N, PIN_IO2_N };
    static const int dedic_out_pins[] = { PIN_DEV_SEL_N };
    dedic_gpio_bundle_handle_t dedic_in_bundle, dedic_out_bundle;
    const dedic_gpio_bundle_config_t in_cfg =
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         *   2. one APB read of GPIO.in (A0-A7; no memw: the last store, the
         *      bus release, left in the previous PHI1);
         *   3. /IO2: c = io2_cur[A0-A7], DEV_SEL_N for this cycle with one
         *      ee.wr_mask_gpio_out (the VERA strobes are gated by PHI2 in
         *      hardware);
         *   4. /IO1 read: drive win[A0-A7] at once.  U19 passes it to the C64
         *      because /IO1 enables it (hardware gating).
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        {
            /* VERA drives the bus: sample it just before PHI2 falls. */
            uint32_t last = lo, now;
            while ((now = GPIO.in) & (1UL << PIN_PHI2))
                last = now;
            log_send(EVT_REG, (uint8_t)off8, decode_data(last), 0x00u);
        }
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    cfg.mode         = GPIO_MODE_INPUT;

    /* Bank 0 inputs: PHI2, RW, D0-D7, A0-A9 */
    cfg.pin_bit_mask = (1ULL << PIN_PHI2) | (1ULL << PIN_RW) | DBUS_MASK | ABUS_LO_MASK;
    gpio_config(&cfg);

    /* Bank 1 inputs: A10-A15 (wired, not needed for decode), /IO1, /IO2, CDONE */
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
